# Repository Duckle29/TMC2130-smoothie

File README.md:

# TMC2130-smoothie
W.I.P. put on git because onedrive and linux just won't be friends, and inteded to put it here after it was tested to be working anyways

Untill this has been tested, consider this a steaming pile of trash ;)

Board has now been routed. I had to manually rename the cloned pieces of the circuit, I expect to have swapped some things on accident. I might not, that'd be great, but I have to go over and check that first.

renders:

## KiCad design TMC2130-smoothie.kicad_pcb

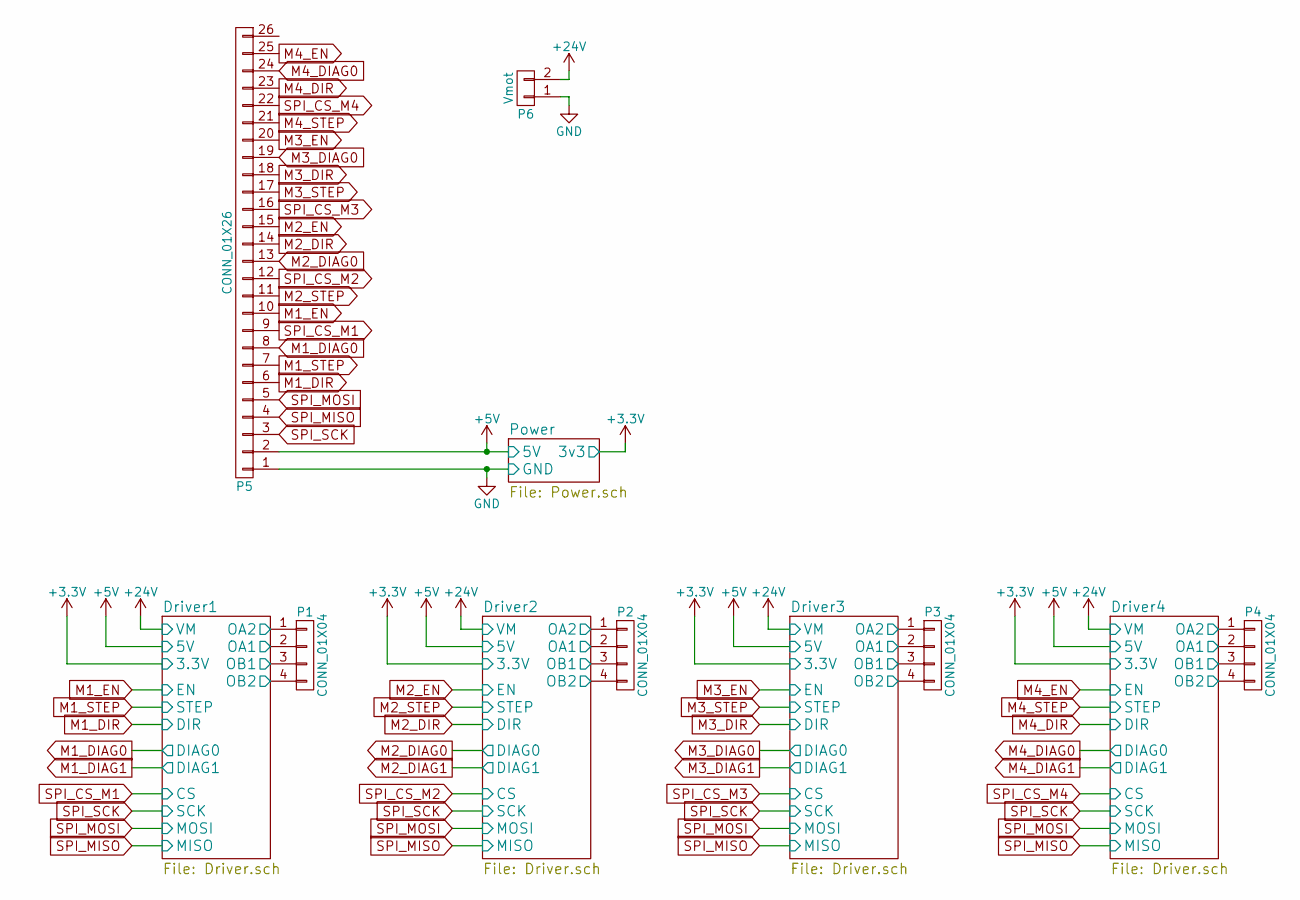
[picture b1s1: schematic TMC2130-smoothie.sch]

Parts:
P1, P2, P3, P4: CONN_01X04; Pin_Header_Straight_1x04
P5: CONN_01X26; Pin_Header_Straight_2x13_Pitch1.27mm_SMD
P6: Vmot; AK300-2

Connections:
+5V: P5.2; also elsewhere on the board
+24V: P6.2; also elsewhere on the board
/Driver1/OA1: P1.2; also elsewhere on the board
/Driver1/OA2: P1.1; also elsewhere on the board
/Driver1/OB1: P1.3; also elsewhere on the board
/Driver1/OB2: P1.4; also elsewhere on the board
/Driver2/OA1: P2.2; also elsewhere on the board
/Driver2/OA2: P2.1; also elsewhere on the board
/Driver2/OB1: P2.3; also elsewhere on the board
/Driver2/OB2: P2.4; also elsewhere on the board
/Driver3/OA1: P3.2; also elsewhere on the board
/Driver3/OA2: P3.1; also elsewhere on the board
/Driver3/OB1: P3.3; also elsewhere on the board
/Driver3/OB2: P3.4; also elsewhere on the board
/Driver4/OA1: P4.2; also elsewhere on the board
/Driver4/OA2: P4.1; also elsewhere on the board
/Driver4/OB1: P4.3; also elsewhere on the board
/Driver4/OB2: P4.4; also elsewhere on the board
GND: P5.1, P6.1; also elsewhere on the board
M1_DIAG0: P5.8; also elsewhere on the board
M1_DIR: P5.6; also elsewhere on the board
M1_EN: P5.10; also elsewhere on the board
M1_STEP: P5.7; also elsewhere on the board
M2_DIAG0: P5.13; also elsewhere on the board
M2_DIR: P5.14; also elsewhere on the board
M2_EN: P5.15; also elsewhere on the board
M2_STEP: P5.11; also elsewhere on the board
M3_DIAG0: P5.19; also elsewhere on the board
M3_DIR: P5.18; also elsewhere on the board
M3_EN: P5.20; also elsewhere on the board
M3_STEP: P5.17; also elsewhere on the board
M4_DIAG0: P5.24; also elsewhere on the board
M4_DIR: P5.23; also elsewhere on the board
M4_EN: P5.25; also elsewhere on the board
M4_STEP: P5.21; also elsewhere on the board
SPI_CS_M1: P5.9; also elsewhere on the board
SPI_CS_M2: P5.12; also elsewhere on the board
SPI_CS_M3: P5.16; also elsewhere on the board
SPI_CS_M4: P5.22; also elsewhere on the board
SPI_MISO: P5.4; also elsewhere on the board
SPI_MOSI: P5.5; also elsewhere on the board
SPI_SCK: P5.3; also elsewhere on the board

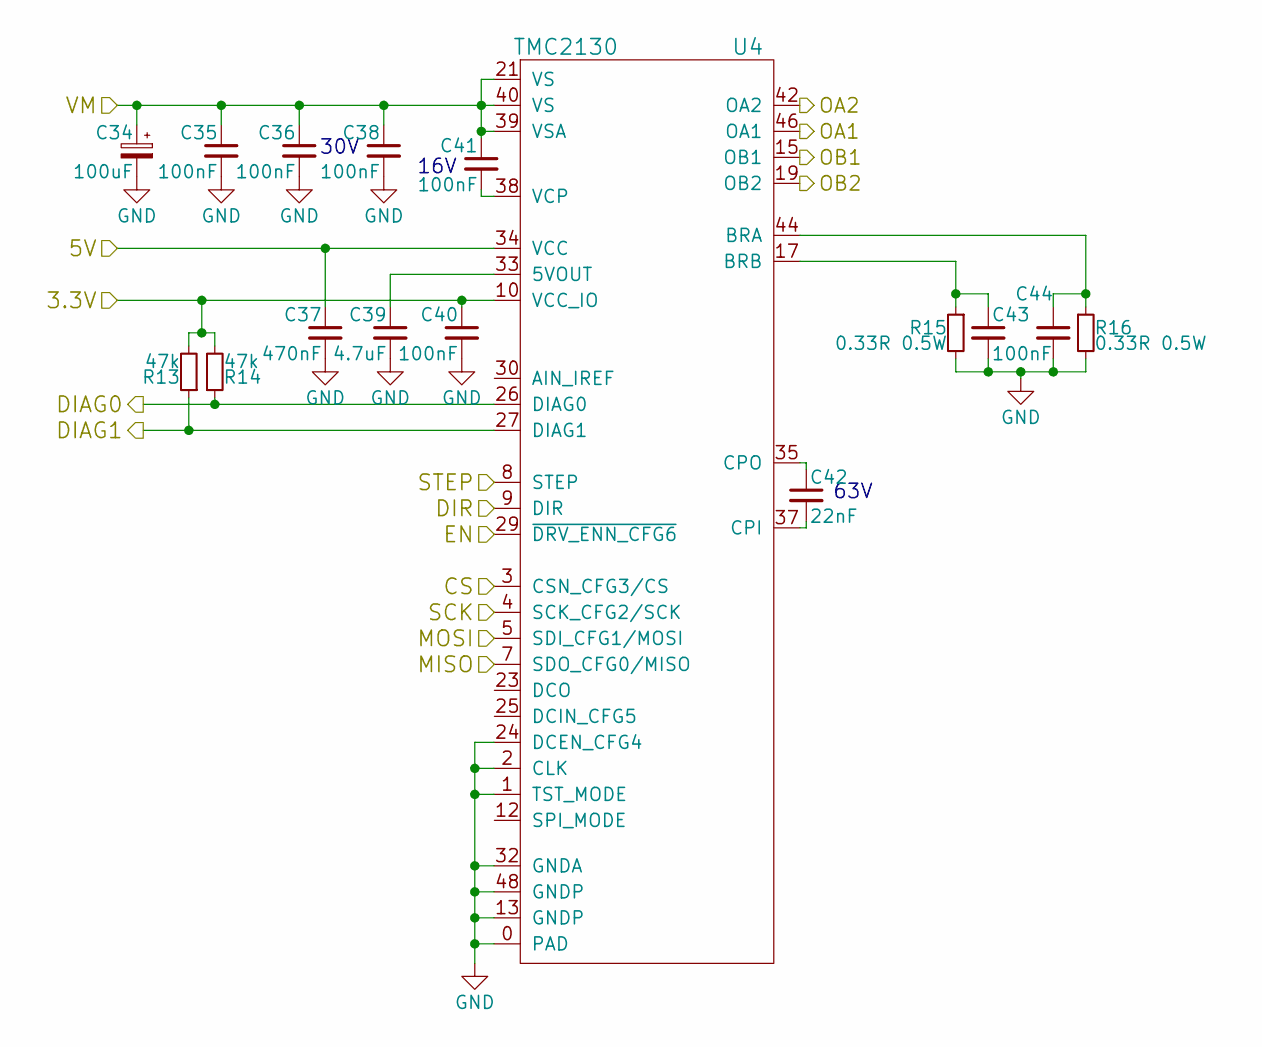
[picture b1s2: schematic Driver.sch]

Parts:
C1: 100uF; CP_Elec_8x10
C2, C3, C5, C7, C8, C10, C11: 100nF; C_0603_HandSoldering
C4: 470nF; C_0603_HandSoldering
C6: 4.7uF; C_0805_HandSoldering
C9: 22nF; C_0603_HandSoldering
R1, R2: 47k; R_0603_HandSoldering
R3, R4: 0.33R 0.5W; R_1210_HandSoldering
U1: TMC2130; TMC2130-TQFP

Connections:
+3V3: C7.1, R1.2, R2.2, U1.10 (VCC_IO); also elsewhere on the board
+5V: C4.1, U1.34 (VCC); also elsewhere on the board
+24V: C1.1, C2.1, C3.1, C5.1, C8.1, U1.21 (VS), U1.39 (VSA), U1.40 (VS); also elsewhere on the board
/Driver1/OA1: U1.46 (OA1); also elsewhere on the board
/Driver1/OA2: U1.42 (OA2); also elsewhere on the board
/Driver1/OB1: U1.15 (OB1); also elsewhere on the board
/Driver1/OB2: U1.19 (OB2); also elsewhere on the board
GND: C1.2, C2.2, C3.2, C4.2, C5.2, C6.2, C7.2, C10.2, C11.2, R3.2, R4.2, U1.0 (PAD), U1.1 (TST_MODE), U1.2 (CLK), U1.13 (GNDP), U1.24 (DCEN_CFG4), U1.32 (GNDA), U1.48 (GNDP); also elsewhere on the board
M1_DIAG0: R2.1, U1.26 (DIAG0); also elsewhere on the board
M1_DIAG1: R1.1, U1.27 (DIAG1)
M1_DIR: U1.9 (DIR); also elsewhere on the board
M1_EN: U1.29 (~DRV_ENN_CFG6); also elsewhere on the board
M1_STEP: U1.8 (STEP); also elsewhere on the board
unnamed: C6.1, U1.33 (5VOUT)
unnamed: C8.2, U1.38 (VCP)
unnamed: C9.1, U1.35 (CPO)
unnamed: C9.2, U1.37 (CPI)
unnamed: C10.1, R3.1, U1.17 (BRB)
unnamed: C11.1, R4.1, U1.44 (BRA)
SPI_CS_M1: U1.3 (CSN_CFG3/CS); also elsewhere on the board
SPI_MISO: U1.7 (SDO_CFG0/MISO); also elsewhere on the board
SPI_MOSI: U1.5 (SDI_CFG1/MOSI); also elsewhere on the board
SPI_SCK: U1.4 (SCK_CFG2/SCK); also elsewhere on the board

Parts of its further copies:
C12, C23, C34: 100uF; CP_Elec_8x10
C13, C14, C16, C18, C19, C21, C22, C24, C25, C27, C29, C30, C32, C33, C35, C36, C38, C40, C41, C43, C44: 100nF; C_0603_HandSoldering
C15, C26, C37: 470nF; C_0603_HandSoldering
C17, C28, C39: 4.7uF; C_0805_HandSoldering
C20, C31, C42: 22nF; C_0603_HandSoldering
R5, R6, R9, R10, R13, R14: 47k; R_0603_HandSoldering
R7, R8, R11, R12, R15, R16: 0.33R 0.5W; R_1210_HandSoldering
U2, U3, U4: TMC2130; TMC2130-TQFP

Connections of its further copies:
+3V3: C18.1, C29.1, C40.1, R5.2, R6.2, R9.2, R10.2, R13.2, R14.2, U2.10 (VCC_IO), U3.10 (VCC_IO), U4.10 (VCC_IO); also elsewhere on the board
+5V: C15.1, C26.1, C37.1, U2.34 (VCC), U3.34 (VCC), U4.34 (VCC); also elsewhere on the board
+24V: C12.1, C13.1, C14.1, C16.1, C19.1, C23.1, C24.1, C25.1, C27.1, C30.1, C34.1, C35.1, C36.1, C38.1, C41.1, U2.21 (VS), U2.39 (VSA), U2.40 (VS), U3.21 (VS), U3.39 (VSA), U3.40 (VS), U4.21 (VS), U4.39 (VSA), U4.40 (VS); also elsewhere on the board
/Driver2/OA1: U2.46 (OA1); also elsewhere on the board
/Driver2/OA2: U2.42 (OA2); also elsewhere on the board
/Driver2/OB1: U2.15 (OB1); also elsewhere on the board
/Driver2/OB2: U2.19 (OB2); also elsewhere on the board
/Driver3/OA1: U3.46 (OA1); also elsewhere on the board
/Driver3/OA2: U3.42 (OA2); also elsewhere on the board
/Driver3/OB1: U3.15 (OB1); also elsewhere on the board
/Driver3/OB2: U3.19 (OB2); also elsewhere on the board
/Driver4/OA1: U4.46 (OA1); also elsewhere on the board
/Driver4/OA2: U4.42 (OA2); also elsewhere on the board
/Driver4/OB1: U4.15 (OB1); also elsewhere on the board
/Driver4/OB2: U4.19 (OB2); also elsewhere on the board
GND: C12.2, C13.2, C14.2, C15.2, C16.2, C17.2, C18.2, C21.2, C22.2, C23.2, C24.2, C25.2, C26.2, C27.2, C28.2, C29.2, C32.2, C33.2, C34.2, C35.2, C36.2, C37.2, C38.2, C39.2, C40.2, C43.2, C44.2, R7.2, R8.2, R11.2, R12.2, R15.2, R16.2, U2.0 (PAD), U2.1 (TST_MODE), U2.2 (CLK), U2.13 (GNDP), U2.24 (DCEN_CFG4), U2.32 (GNDA), U2.48 (GNDP), U3.0 (PAD), U3.1 (TST_MODE), U3.2 (CLK), U3.13 (GNDP), U3.24 (DCEN_CFG4), U3.32 (GNDA), U3.48 (GNDP), U4.0 (PAD), U4.1 (TST_MODE), U4.2 (CLK), U4.13 (GNDP), U4.24 (DCEN_CFG4), U4.32 (GNDA), U4.48 (GNDP); also elsewhere on the board
M2_DIAG0: R6.1, U2.26 (DIAG0); also elsewhere on the board
M2_DIAG1: R5.1, U2.27 (DIAG1)
M2_DIR: U2.9 (DIR); also elsewhere on the board
M2_EN: U2.29 (~DRV_ENN_CFG6); also elsewhere on the board
M2_STEP: U2.8 (STEP); also elsewhere on the board
M3_DIAG0: R10.1, U3.26 (DIAG0); also elsewhere on the board
M3_DIAG1: R9.1, U3.27 (DIAG1)
M3_DIR: U3.9 (DIR); also elsewhere on the board
M3_EN: U3.29 (~DRV_ENN_CFG6); also elsewhere on the board
M3_STEP: U3.8 (STEP); also elsewhere on the board
M4_DIAG0: R14.1, U4.26 (DIAG0); also elsewhere on the board
M4_DIAG1: R13.1, U4.27 (DIAG1)
M4_DIR: U4.9 (DIR); also elsewhere on the board
M4_EN: U4.29 (~DRV_ENN_CFG6); also elsewhere on the board
M4_STEP: U4.8 (STEP); also elsewhere on the board
unnamed: C17.1, U2.33 (5VOUT)
unnamed: C19.2, U2.38 (VCP)
unnamed: C20.1, U2.35 (CPO)
unnamed: C20.2, U2.37 (CPI)
unnamed: C21.1, R7.1, U2.17 (BRB)
unnamed: C22.1, R8.1, U2.44 (BRA)
unnamed: C28.1, U3.33 (5VOUT)
unnamed: C30.2, U3.38 (VCP)
unnamed: C31.1, U3.35 (CPO)
unnamed: C31.2, U3.37 (CPI)
unnamed: C32.1, R11.1, U3.17 (BRB)
unnamed: C33.1, R12.1, U3.44 (BRA)
unnamed: C39.1, U4.33 (5VOUT)
unnamed: C41.2, U4.38 (VCP)
unnamed: C42.1, U4.35 (CPO)
unnamed: C42.2, U4.37 (CPI)
unnamed: C43.1, R15.1, U4.17 (BRB)
unnamed: C44.1, R16.1, U4.44 (BRA)
SPI_CS_M2: U2.3 (CSN_CFG3/CS); also elsewhere on the board
SPI_CS_M3: U3.3 (CSN_CFG3/CS); also elsewhere on the board
SPI_CS_M4: U4.3 (CSN_CFG3/CS); also elsewhere on the board
SPI_MISO: U2.7 (SDO_CFG0/MISO), U3.7 (SDO_CFG0/MISO), U4.7 (SDO_CFG0/MISO); also elsewhere on the board
SPI_MOSI: U2.5 (SDI_CFG1/MOSI), U3.5 (SDI_CFG1/MOSI), U4.5 (SDI_CFG1/MOSI); also elsewhere on the board
SPI_SCK: U2.4 (SCK_CFG2/SCK), U3.4 (SCK_CFG2/SCK), U4.4 (SCK_CFG2/SCK); also elsewhere on the board

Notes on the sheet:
16V
30V
63V

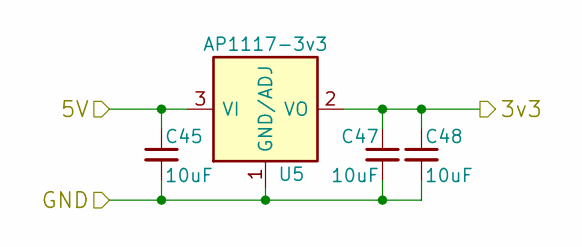
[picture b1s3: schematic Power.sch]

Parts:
C45, C47, C48: 10uF; C_0805_HandSoldering
U5: AP1117-3v3; SOT-223-3Lead_TabPin2

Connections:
+3V3: C47.1, C48.1, U5.2 (VO); also elsewhere on the board
+5V: C45.1, U5.3 (VI); also elsewhere on the board
GND: C45.2, C47.2, C48.2, U5.1 (GND/ADJ); also elsewhere on the board

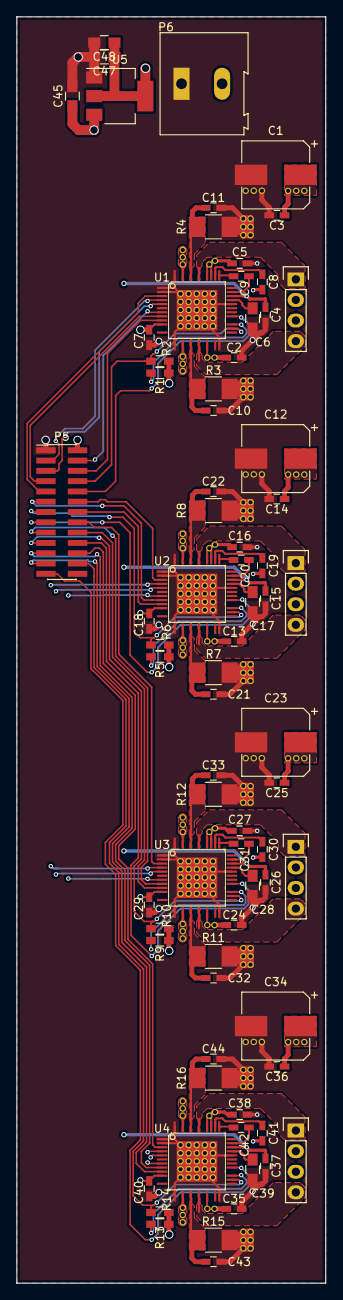
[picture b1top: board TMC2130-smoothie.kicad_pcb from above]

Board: 4 copper layers, 38.1 x 156.2 mm, 74 parts (0 on the bottom side), 71 nets.

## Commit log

2017-10-06 Started routing drivers
2017-10-07 Initial layout of 1-driver
2017-10-07 Routed entire PCB
2017-10-07 Added renders
2017-10-07 Added renders to readme
2017-10-07 Added gerbers
